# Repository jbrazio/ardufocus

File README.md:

**Ardufocus - The most accurate Open Source focus controller.**

Ardufocus is the only OSS/OSH controller supporting **two independent** focusing motors, **high resolution**
mode allowing **sub μm** movements by step, multiple acceleration profiles and it will never forget your
focuser position between restarts.

Ardufocus is a multi repository project:
- [Ardufocus firmware](https://github.com/jbrazio/ardufocus)
- [Ardufocus schematics](https://github.com/jbrazio/ardufocus-schematics)
- [Ardufocus ASCOM IFocuserV3 Driver](https://github.com/jbrazio/ardufocus-ascom)

Ardufocus is licensed under [GNU GPLv3](https://www.gnu.org/licenses/gpl-3.0.en.html). <br />
Ardufocus PCB schematics are licensed under [CC BY-NC-SA 4.0](https://creativecommons.org/licenses/by-nc-sa/4.0/).

----

### For documentation, tutorials and howto visit [ardufocus.com](https://ardufocus.com).

----

**Support this project**
- Paypal: jbrazio@gmail.com
- Bitcoin: bc1qfkl2zgdjpn6993xma4pl5yhr5cdunu9sa0g8vp
- Ethereum: 0xdfDfFAf0EF66fC896F0907c8C09180a5c74eE8fA

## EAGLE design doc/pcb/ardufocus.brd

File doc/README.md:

----

### For documentation, tutorials and howto visit [ardufocus.com](https://ardufocus.com).

----

# Disclaimer

Unless otherwise noted, all materials contained in this repository are copyrighted
Copyright (C) 2017-2019 João Brázio [joao@brazio.org] and licensed under GPLv3.

The following materials are property of their respective owners:

- moonlite/

## Fair Use

Copyright Disclaimer under section 107 of the Copyright Act of 1976, allowance
is made for "fair use" for purposes such as criticism, comment, news reporting,
teaching, scholarship, education and research.

## Fair Use Definition

Fair use is a doctrine in United States copyright law that allows limited use
of copyrighted material without requiring permission from the rights holders,
such as commentary, criticism, news reporting, research, teaching or scholarship.
It provides for the legal, non-licensed citation or incorporation of copyrighted
material in another author’s work under a four-factor balancing test.

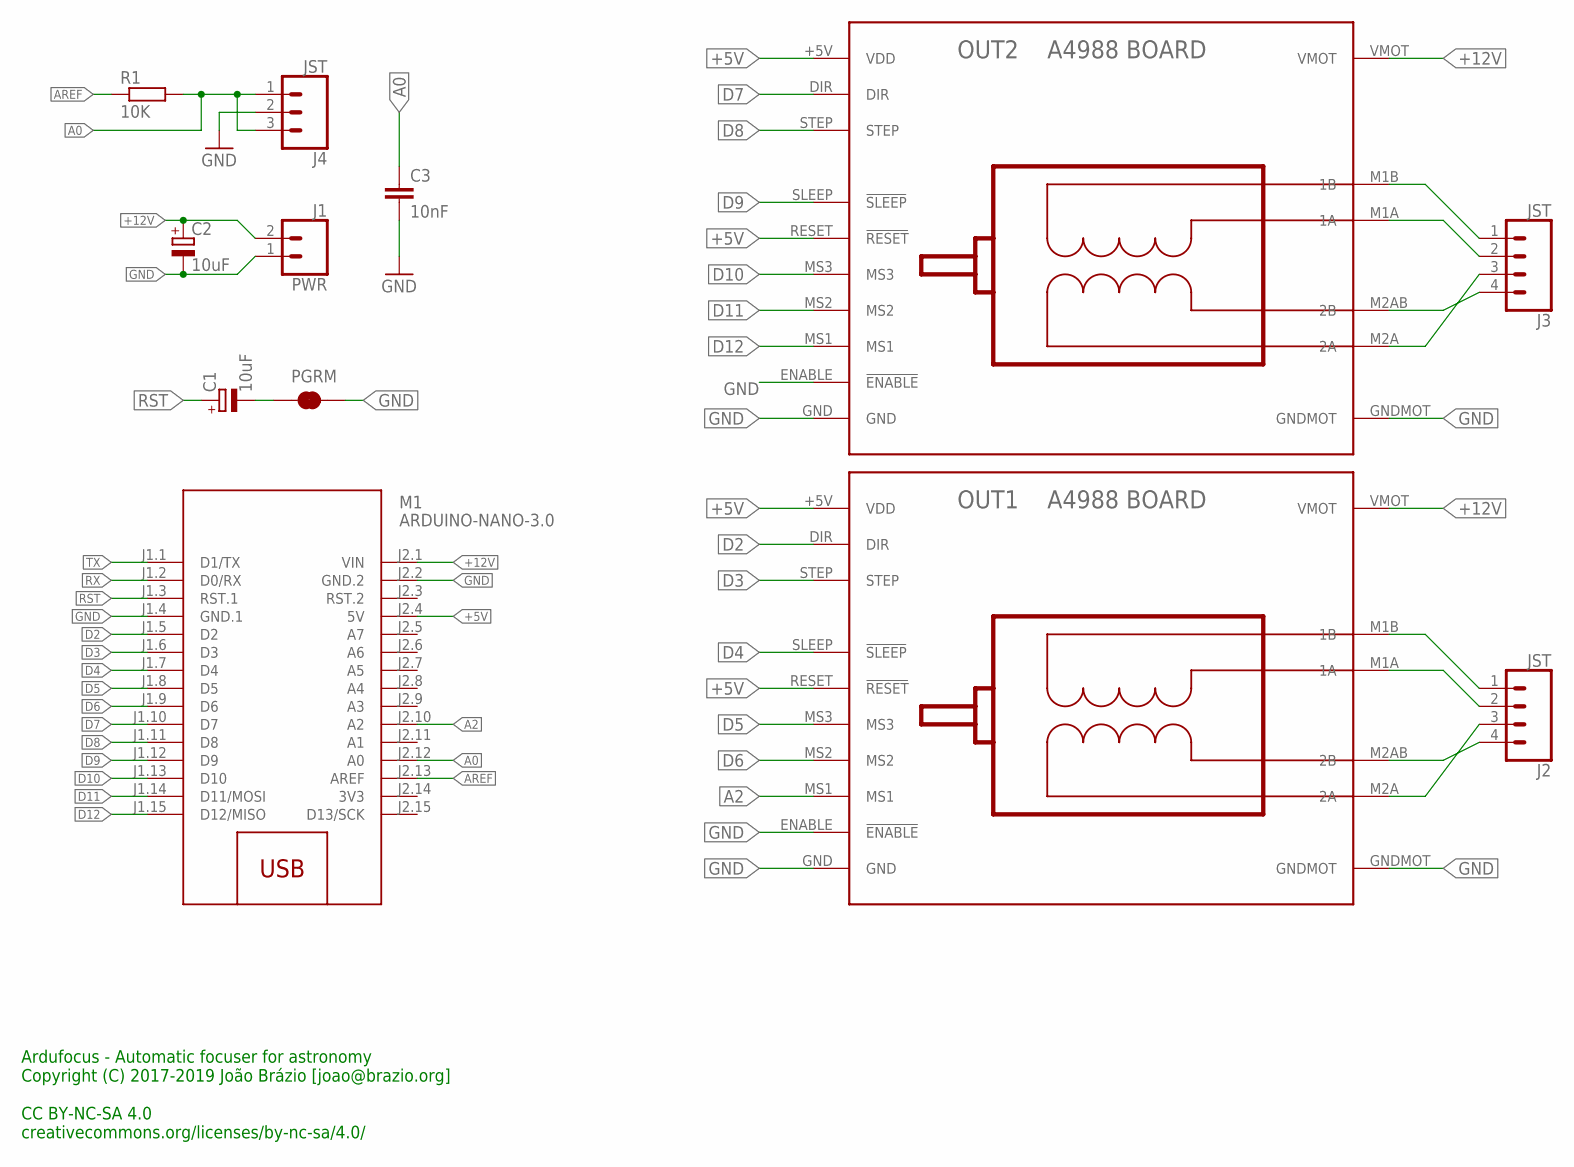
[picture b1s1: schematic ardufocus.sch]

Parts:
C1: 10uF; E1,8-4
C2: 10uF; E2,5-6E
C3: 10nF; C3216
J1: PWR; SCREWTERMINAL-5MM-2
J2, J3: JST; JST-4-PTH-VERT
J4: JST; JST-3-PTH-VERT
M1: ARDUINO-NANO-3.0
OUT1, OUT2: BOARD_A4988
PGRM: JUMPER-SMT_2_NC_TRACE_SILK; SMT-JUMPER_2_NC_TRACE_SILK
R1: 10K; M1206

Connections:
3V3: M1.J2.14 (3V3)
+5V: M1.J2.4 (5V), OUT1.+5V (VDD), OUT1.RESET (!RESET), OUT2.+5V (VDD), OUT2.RESET (!RESET)
+12V: C2.+, J1.2, M1.J2.1 (VIN), OUT1.VMOT, OUT2.VMOT
A0: C3.1, J4.1, J4.3, M1.J2.12 (A0), R1.2
A2: M1.J2.10 (A2), OUT1.MS1
AREF: M1.J2.13 (AREF), R1.1
D2: M1.J1.5 (D2), OUT1.DIR
D3: M1.J1.6 (D3), OUT1.STEP
D4: M1.J1.7 (D4), OUT1.SLEEP (!SLEEP)
D5: M1.J1.8 (D5), OUT1.MS3
D6: M1.J1.9 (D6), OUT1.MS2
D7: M1.J1.10 (D7), OUT2.DIR
D8: M1.J1.11 (D8), OUT2.STEP
D9: M1.J1.12 (D9), OUT2.SLEEP (!SLEEP)
D10: M1.J1.13 (D10), OUT2.MS3
D11: M1.J1.14 (D11/MOSI), OUT2.MS2
D12: M1.J1.15 (D12/MISO), OUT2.MS1
GND: C2.-, C3.2, J1.1, J4.2, M1.J1.4 (GND.1), M1.J2.2 (GND.2), OUT1.ENABLE (!ENABLE), OUT1.GND, OUT1.GNDMOT, OUT2.ENABLE (!ENABLE), OUT2.GND, OUT2.GNDMOT, PGRM.2
unnamed: J3.1, OUT2.M1B (1B)
unnamed: C1.-, PGRM.1
unnamed: J2.3, OUT1.M2A (2A)
unnamed: J3.2, OUT2.M1A (1A)
unnamed: J3.4, OUT2.M2AB (2B)
unnamed: J2.1, OUT1.M1B (1B)
unnamed: J2.2, OUT1.M1A (1A)
unnamed: J2.4, OUT1.M2AB (2B)
unnamed: J3.3, OUT2.M2A (2A)
RST: C1.+, M1.J1.3 (RST.1)
RX: M1.J1.2 (D0/RX)
TX: M1.J1.1 (D1/TX)

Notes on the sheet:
Ardufocus - Automatic focuser for astronomy Copyright (C) 2017-2019 João Brázio [joao@brazio.org] CC BY-NC-SA 4.0 creativecommons.org/licenses/by-nc-sa/4.0/

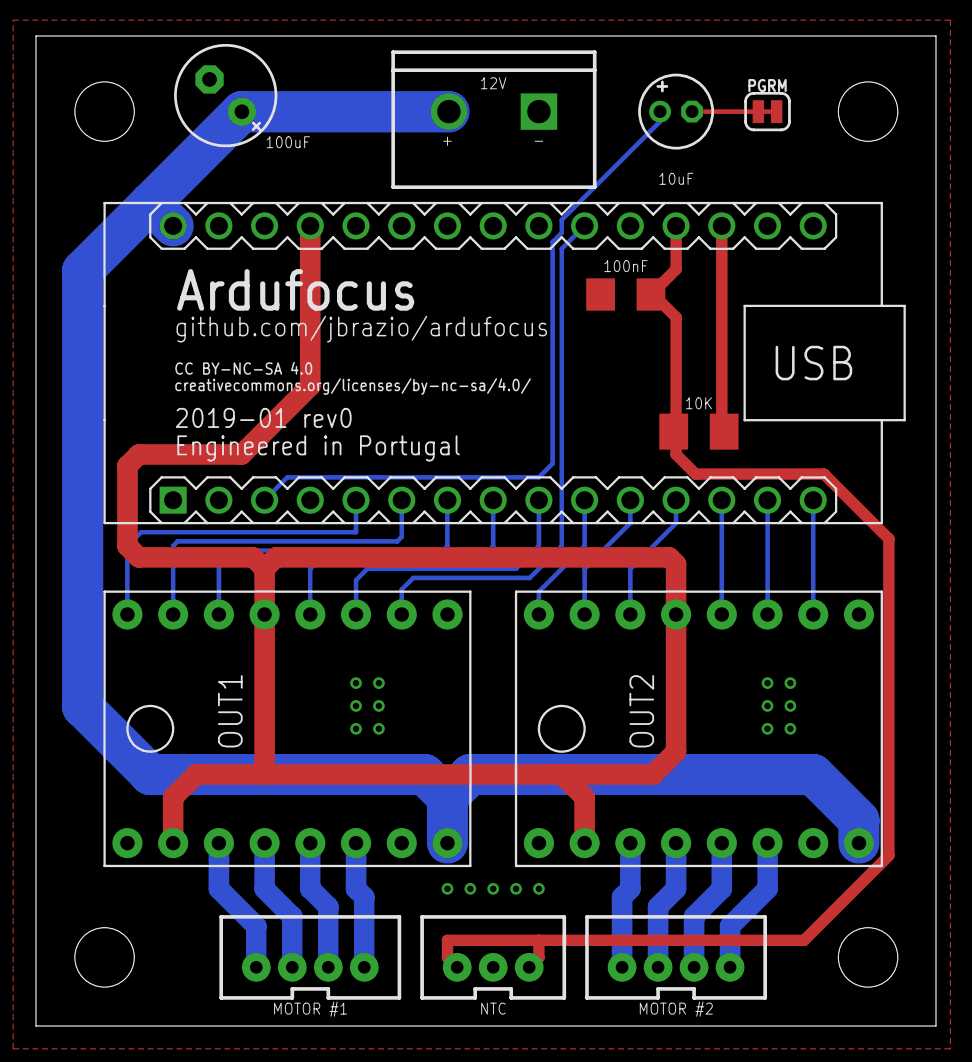
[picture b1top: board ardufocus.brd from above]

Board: 2 copper layers, 50.0 x 55.0 mm, 16 parts (0 on the bottom side), 27 nets.

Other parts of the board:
U$1, U$2, U$3, U$4: STAND-OFF

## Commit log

2017-07-14 Project init and import
2017-07-14 Added Bipolar schematic
2017-07-14 Adds missing credit
2017-07-21 Documented SGP settings for bipolar config
2017-07-21 Doc folder cleanup
2017-07-21 Documented the 3D objects
2017-07-21 Replaced obj preview files with a smaller version
2017-07-21 Added BOM list
2017-08-31 New flag to define the direction of the motor rotation
2017-08-31 A4988: Improvement on the step() function
2017-09-03 Cleanup ul2003 class
2017-09-03 Implemented trapezoidal accel profile
2017-09-29 A4988: Uses a 50% duty cycle
2017-11-19 Adds support for the Arduino IDE
2017-11-19 Microstep selection mode improvement
2017-11-19 Update the documentation
2017-11-21 Updated the schematic and breadboard layout
2017-12-11 Update the project's documentation
2018-01-03 Major code refactoring
2018-01-03 Added stl info for printing the enclosure
2018-01-03 Typo correction
2018-03-15 Stepping optimization for the A4988 driver
2018-03-15 New Platformio ASM debug target
2018-03-15 Added native targets to default Platformio build
2018-03-15 Implemented the remote reset command
2018-03-15 Implemented IO::read()
2018-03-15 Implemented half-step compression
2018-03-16 Send serial hex value in upper case
2018-05-04 Add support for more microcontrollers (ATMega128/328)
2018-05-04 Move sketch to appropriately named subfolder
    The Arduino IDE requires that a sketch be located in a folder of the same name. Although the name of the repository does match the sketch name, when GitHub's popular Clone or download > Download ZIP 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
    When opening a file that does not meet this sketch/folder name matching requirement the Arduino IDE presents a dialog:
    The file "ardufocus.ino" needs to be inside a sketch folder named "ardufocus".
    Create this folder, move the file, and continue?
    After clicking "OK" the Arduino IDE currently moves only the file
2018-05-17 Source tree simplification
2018-05-17 Sane default configuration
2018-05-17 SGP wrong temp workaround
2018-06-07 Update HAL
2018-06-07 Renamed conditionals to assert
2018-06-08 Stepper classes code improvement
2018-06-11 Implements acceleration profiles: linear, trapezoid and s-curve
2018-06-14 No shared config for instances of the same class
2018-06-14 CI improvement and some folder re-struct
2018-06-14 Minor serial tweaks
2018-06-15 Migration to timer0 with fixed ISR frequency
2018-06-15 Implemented sleep timeout
2018-06-20 Fixes config.h assert errors
2018-09-03 Convert constant integer to floating point
2018-09-03 Update the source code location
2018-09-03 Adds support for DRV8825 driver
2018-10-07 Code clean up and minor refactoring
2018-10-16 Sync default driver pinout to the wiring diagram
2018-10-19 Automatic save config to EEPROM
2018-10-22 EEPROM cfg struct no longer needs hardcoded size
2019-01-26 Added Eagle PCB and Schematic
2019-03-18 Update copyright notice
2019-03-18 Fix travis build error
2019-03-24 High resolution mode and some misc changes
2019-03-25 Quick workaround for __cxa_pure_virtual linker error
2019-04-08 motor_is_moving() was not protocol compliant
2019-04-08 DTR auto-reset feature
2019-04-09 Second motor control is fully functional
2019-04-09 Removed local config support
2019-04-09 A4988 ASCII schematic
2019-04-12 Fixed ISR timming when two motors were active, removed COMPRESSION and some other small fixes
2019-04-15 Include cleanup and IO lib diet
2019-04-15 Probot Stale implementaion
2019-04-16 Update the README file
2019-04-18 Update main logo
2019-04-18 Implement sleep() for ULN2003
2019-04-18 Update Travis CI badge
2019-05-07 DTR flag is now saved on-change
2019-05-08 Implements #9: New HAL for ATmega32U4
2019-05-08 Update version tag
2019-06-17 Fixed a typo on config.h
2019-06-22 Improves the analog class as discussed at #5
2019-06-23 Implements Keys and Pot (KAP) user interface
2019-06-25 New UI keyboard class
2019-06-25 Better handling for User Interface classes
2019-06-26 Smoother stepper by lowering Analog ISR priority
2019-06-28 Removed runtime software microstepping switch
2019-06-28 Fix travis error when building
2019-06-28 START_TEMP_CONVERSION_ON_EVERY_GET has been deprecated
2019-06-28 Documentation cleanup
2019-06-28 Improved Travis build matrix
2019-06-28 Fixes an error with KAP due to leftover debug functions
2019-06-28 Fixes an error with Travis build script
2021-11-21 Ignore more PlatformIO local files and VSCode files.
2021-11-21 Make serial monitor do echo and send only on enter.
2021-11-21 Configure breadboard pins for my layout
2021-11-21 Add higher resolution methods for A4988
2021-11-21 Fix MOTOR1_MAX_SPEED
2021-11-21 Support configuring microstepping in the A4988 driver
2021-11-25 Add support for LM335 temperature sensor
    - Added new define TEMP_USE_LM335 to config.h
    - Changes when this define is active:
    - ADC reference voltage set to 5.0V
    - A new util function is used to convert to deg C
2022-01-07 A lot of changes
2022-01-07 Update travis python version
2022-01-08 Update travis config
2023-11-09 Added motor speed to EEPROM
2023-11-09 Added half step mode to EEPROM
2023-11-11 Added speed and stepper mode saving to EEPROM (#35)
    * Added motor speed to EEPROM
    * Added half step mode to EEPROM
2026-05-28 Update Jekyll source path in workflow
    Change Jekyll source directory for GitHub Pages deployment.
2026-05-28 Import website

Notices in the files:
parts and their libraries:
SparkFun-Connectors: Licensing: Creative Commons ShareAlike 4.0 International - https://creativecommons.org/licenses/by-sa/4.0
diy-modules: Released under the Creative Commons Attribution 4.0 International License: http://creativecommons.org/licenses/by/4.0
